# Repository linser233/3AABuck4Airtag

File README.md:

# 3AABuck4Airtag
3AA to 3V Ultra Low IQ Buck For Airtag or Findmy and other IOT uses, with a theoretical range of up to 10 years.
**Validated**

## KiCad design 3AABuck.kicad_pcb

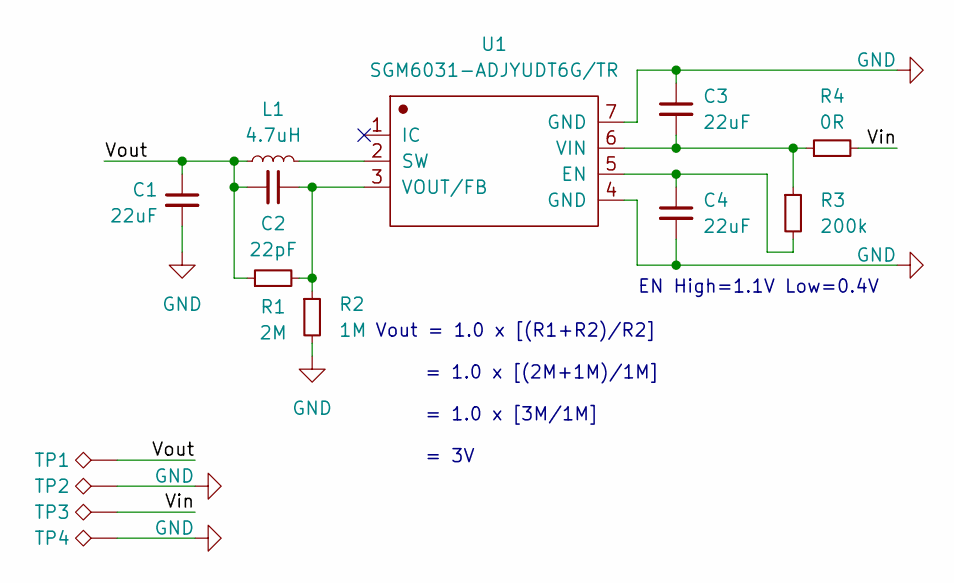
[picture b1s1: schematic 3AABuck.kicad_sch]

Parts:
C1, C3, C4: 22uF; C_0603_1608Metric_Pad1.08x0.95mm_HandSolder
C2: 22pF; C_0603_1608Metric_Pad1.08x0.95mm_HandSolder
L1: 4.7uH; L_Cenker_CKCS8040
R1: 2M; R_0603_1608Metric_Pad0.98x0.95mm_HandSolder
R2: 1M; R_0603_1608Metric_Pad0.98x0.95mm_HandSolder
R3: 200k; R_0603_1608Metric_Pad0.98x0.95mm_HandSolder
R4: 0R; R_0603_1608Metric_Pad0.98x0.95mm_HandSolder
TP1, TP2: TP; TestPoint_Pad_2.0x2.0mm
TP3, TP4: TP; TestPoint_THTPad_3.0x3.0mm_Drill1.5mm
U1: SGM6031-ADJYUDT6G/TR; UTDFN-6L_L2.0-W1.5-P0.50-LS2.6-BL-EP

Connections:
/Vin: R4.2, TP3.1
/Vout: C1.1, C2.2, L1.1, R1.1, TP1.1
GND: C1.2, C3.1, C4.2, R2.2, TP2.1, TP4.1, U1.4 (GND), U1.7 (GND)
unnamed: C4.1, R3.2, U1.5 (EN)
unnamed: L1.2, U1.2 (SW)
unnamed: C3.2, R3.1, R4.1, U1.6 (VIN)
unnamed: C2.1, R1.2, R2.1, U1.3 (VOUT/FB)

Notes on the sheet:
EN High=1.1V Low=0.4V
Vout = 1.0 x [(R1+R2)/R2] = 1.0 x [(2M+1M)/1M] = 1.0 x [3M/1M] = 3V

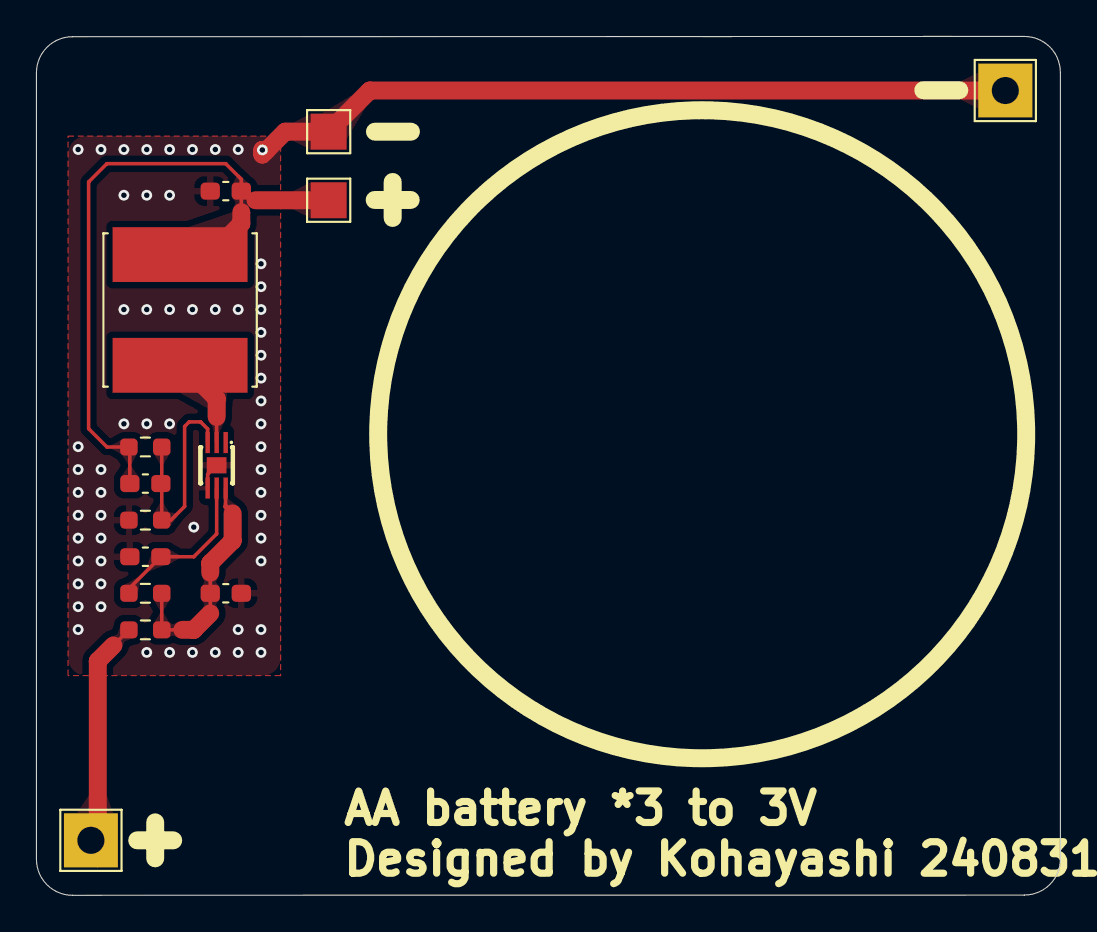
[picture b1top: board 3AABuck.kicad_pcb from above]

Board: 2 copper layers, 56.9 x 47.7 mm, 14 parts (0 on the bottom side), 7 nets.

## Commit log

2025-03-16 upload project files
